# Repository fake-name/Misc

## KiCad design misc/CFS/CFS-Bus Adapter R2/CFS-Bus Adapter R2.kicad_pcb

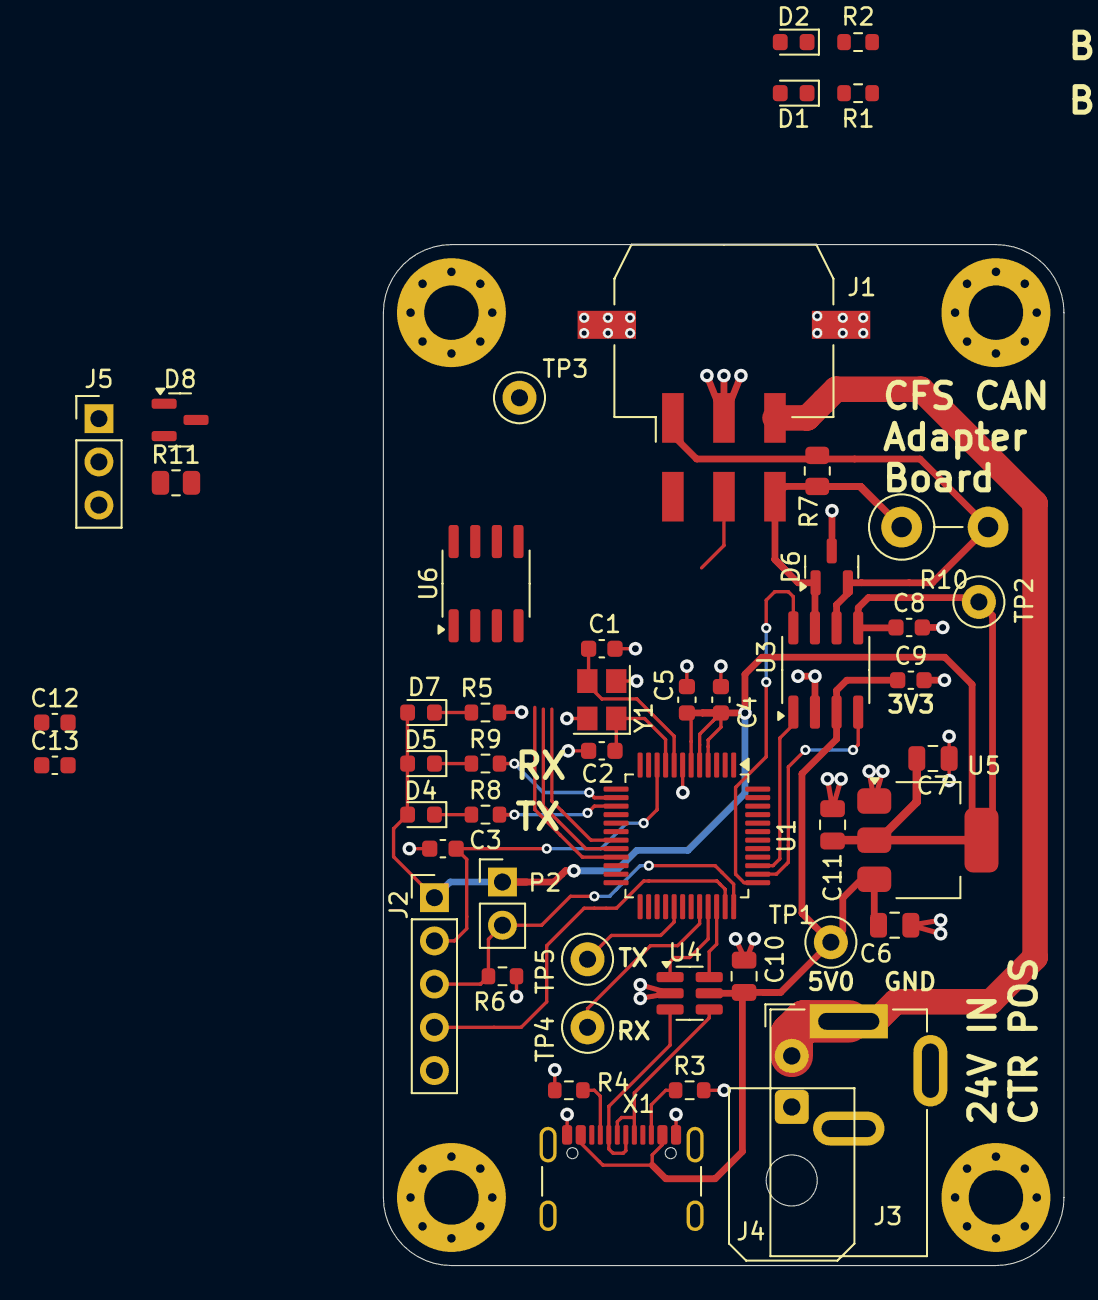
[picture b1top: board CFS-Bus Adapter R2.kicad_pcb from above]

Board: 2 copper layers, 40.0 x 60.0 mm, 53 parts (0 on the bottom side), 36 nets.

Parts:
C1, C2: 6p2_0603_C0G_5%_50V_-40C..125C_Chip-Capacitor; C_0603_1608Metric
C3, C4, C5: 100n; C_0603_1608Metric
C6, C7, C10, C11: 10u_0805_X7R_10%_10V_-40C..125C_Chip-Capacitor; C_0805_2012Metric
C8, C9, C12, C13: 100n_0603_X7R_10%_50V_-40C..125C_Chip-Capacitor; C_0603_1608Metric
D1, D2, D4, D5, D7: LED; LED_0603_1608Metric
D6, D8: NUP2105L; SOT-23
H1, H2, H3, H4: MountingHole; MountingHole_3.2mm_M3_Pad_Via
J1: Conn_02x03_Top_Bottom; Molex_Micro-Fit_3.0_43045-0610_2x03-1MP_P3.00mm_Horizontal
J2: Conn_01x05; PinHeader_1x05_P2.54mm_Vertical
J3: Barrel_Jack_Switch_MountingPin; BarrelJack_GCT_DCJ200-10-A_Horizontal
J4: Conn_01x02; Molex_Micro-Fit_3.0_43045-0200_2x01_P3.00mm_Horizontal
J5: Conn_01x03; PinHeader_1x03_P2.54mm_Vertical
P2: CONN_01X02; PinHeader_1x02_P2.54mm_Vertical
R1, R2: 5k1; R_0603_1608Metric
R3, R4: 5k1_0603_100mW_1%_E24_Chip-Resistor; R_0603_1608Metric
R5, R8, R9: 1k_0603_100mW_1%_E24_Chip-Resistor; R_0603_1608Metric
R6: 10k_0603_100mW_1%_E24_Chip-Resistor; R_0603_1608Metric
R7, R11: 120R_0805_125mW_1%_E24_Chip-Resistor; R_0805_2012Metric
R10: 120R_0805_125mW_1%_E24_Chip-Resistor; R_Axial_DIN0411_L9.9mm_D3.6mm_P5.08mm_Vertical
TP1, TP2, TP3: TP2.0mm; TestPoint_Loop_D1.80mm_Drill1.0mm_Beaded
TP4, TP5: TP1.0mm; TestPoint_Loop_D1.80mm_Drill1.0mm_Beaded
U1: STM32G0B1CBT; LQFP-48_7x7mm_P0.5mm
U3, U6: TJA1051T3; SOIC-8_3.9x4.9mm_P1.27mm
U4: IP4234CZ6; SC-74-6_1.55x2.9mm_P0.95mm
U5: AMS1117-3.3; SOT-223-3_TabPin2
X1: 629722000214_pasteInHole; USB_C_Receptacle_GCT_USB4105-xx-A_16P_TopMnt_Horizontal
Y1: 830108313809; Crystal_SMD_3225-4Pin_3.2x2.5mm

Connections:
+3V3: C4.1, C5.1, C7.1, C8.1, C11.1, C12.1, D4.2 (A), D5.2 (A), D7.2 (A), J2.1, P2.1, TP2.1, U1.4 (VBAT), U1.5 (VREF+), U1.6 (VDD/VDDA), U3.5 (VIO), U5.2 (VO), U6.5 (VIO)
+5V: C6.1, C9.1, C10.1, C13.1, D1.2 (A), D2.2 (A), TP1.1, U3.3 (VCC), U4.5 (VP), U5.3 (VI), U6.3 (VCC), X1.A4 (VBUS), X1.A9 (VBUS), X1.B4 (VBUS), X1.B9 (VBUS)
+24V: J1.3, J3.1, J4.2
/MCU/CAN1_RX: U1.38 (PD0), U3.4 (RXD)
/MCU/CAN1_S: U1.37 (PA15), U3.8 (S)
/MCU/CAN1_TX: U1.39 (PD1), U3.1 (TXD)
/MCU/CAN2_RX: U1.19 (PB0), U6.4 (RXD)
/MCU/CAN2_S: U1.21 (PB2), U6.8 (S)
/MCU/CAN2_TX: U1.20 (PB1), U6.1 (TXD)
/MCU/LED_RX: R9.2, U1.14 (PA3)
/MCU/LED_TX: R8.2, U1.15 (PA4)
/MCU/NRST: C3.1, J2.2, U1.10 (PF2/NRST)
/MCU/RX: TP4.1, U1.32 (PA10)
/MCU/SWCLK: J2.3, P2.2, R6.1, U1.36 (PA14/BOOT0)
/MCU/SWDIO: J2.4, U1.35 (PA13)
/MCU/TX: TP5.1, U1.29 (PA9)
/MCU/USB_{N}: U1.33 (PA11[PA9]), U4.1
/MCU/USB_{P}: U1.34 (PA12[PA10]), U4.6
/RS485-A: D6.1 (K), J1.6, R7.1, R10.1, U3.7 (CANH)
/RS485-B: D6.2 (K), J1.1, R7.2, R10.2, U3.6 (CANL)
/USB_N: U4.3, X1.A7 (DN1), X1.B7 (DN2)
/USB_P: U4.4, X1.A6 (DP1), X1.B6 (DP2)
GND: C1.1, C2.1, C3.2, C4.2, C5.2, C6.2, C7.2, C8.2, C9.2, C10.2, C11.2, C12.2, C13.2, D6.3 (A), D8.3 (A), J1.2, J1.MP, J2.5, J3.2, J3.3, J4.1, J5.2, R3.2, R4.2, R5.2, R6.2, TP3.1, U1.7 (VSS/VSSA), U3.2 (GND), U4.2 (VN), U5.1 (GND), U6.2 (GND), X1.A1 (GND), X1.B1 (GND), Y1.2 (GND), Y1.4 (GND)
unnamed: D1.1 (K), R1.1
unnamed: D2.1 (K), R2.1
unnamed: D4.1 (K), R8.1
unnamed: D5.1 (K), R9.1
unnamed: D7.1 (K), R5.1
unnamed: J1.4, R2.2
unnamed: J1.5, R1.2
unnamed: D8.1 (K), J5.1, R11.2, U6.6 (CANL)
unnamed: D8.2 (K), J5.3, R11.1, U6.7 (CANH)
unnamed: C1.2, U1.8 (PF0/OSC_IN), Y1.3 (C_{2})
unnamed: C2.2, U1.9 (PF1/OSC_OUT), Y1.1 (C_{1})
unnamed: R4.1, X1.A5 (CC1)
unnamed: R3.1, X1.B5 (CC2)

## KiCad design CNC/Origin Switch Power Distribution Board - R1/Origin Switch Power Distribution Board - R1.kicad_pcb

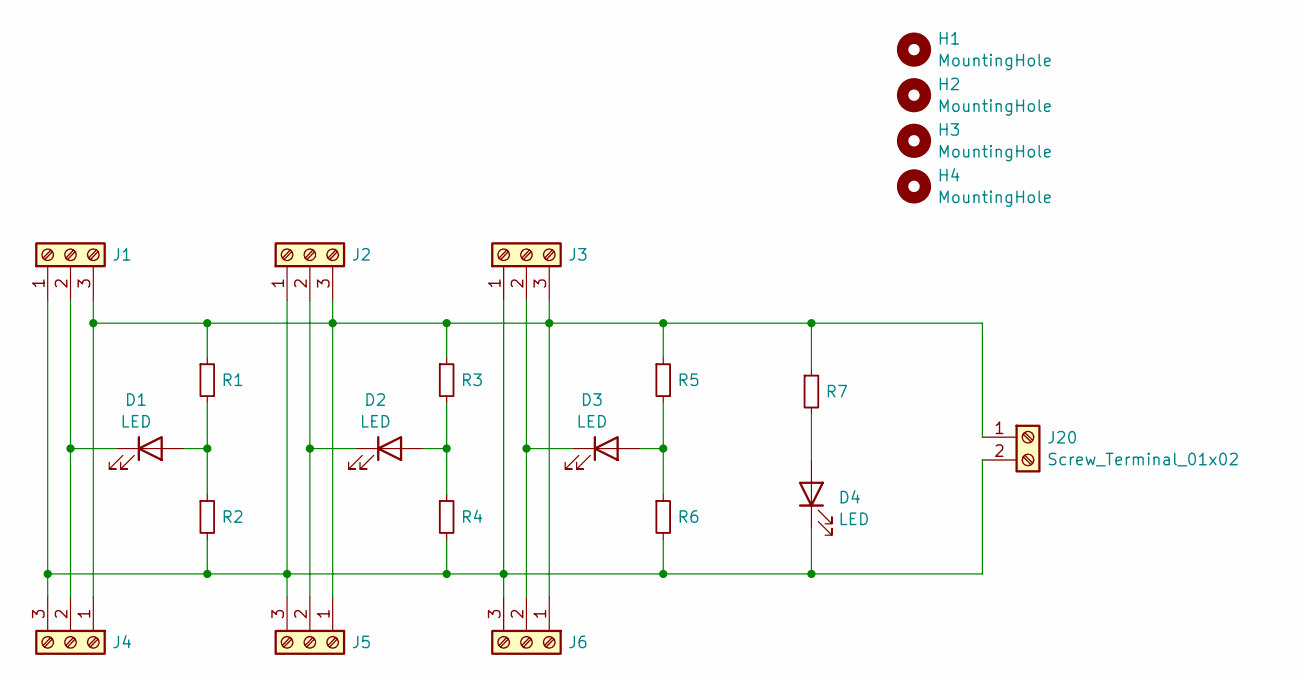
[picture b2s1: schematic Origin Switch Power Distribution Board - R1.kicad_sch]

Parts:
D1, D2, D3, D4: LED; LED_D5.0mm
H1, H2, H3, H4: MountingHole; MountingHole_3.2mm_M3_Pad_Via
J1, J2, J3, J4, J5, J6: Screw_Terminal_01x03; TerminalBlock_Phoenix_MKDS-1,5-3-5.08_1x03_P5.08mm_Horizont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
J20: Screw_Terminal_01x02; TerminalBlock_Phoenix_MKDS-1,5-2-5.08_1x02_P5.08mm_Horizont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
R1, R2, R3, R4, R5, R6, R7: R_Small; R_Axial_DIN0204_L3.6mm_D1.6mm_P7.62mm_Horizontal

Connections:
unnamed: D1.2 (A), R1.2, R2.1
unnamed: D1.1 (K), J1.2, J4.2
unnamed: D2.2 (A), R3.2, R4.1
unnamed: D2.1 (K), J2.2, J5.2
unnamed: D3.2 (A), R5.2, R6.1
unnamed: D3.1 (K), J3.2, J6.2
unnamed: D4.2 (A), R7.2
unnamed: D4.1 (K), J1.1, J2.1, J3.1, J4.3, J5.3, J6.3, J20.2, R2.2, R4.2, R6.2
unnamed: J1.3, J2.3, J3.3, J4.1, J5.1, J6.1, J20.1, R1.1, R3.1, R5.1, R7.1

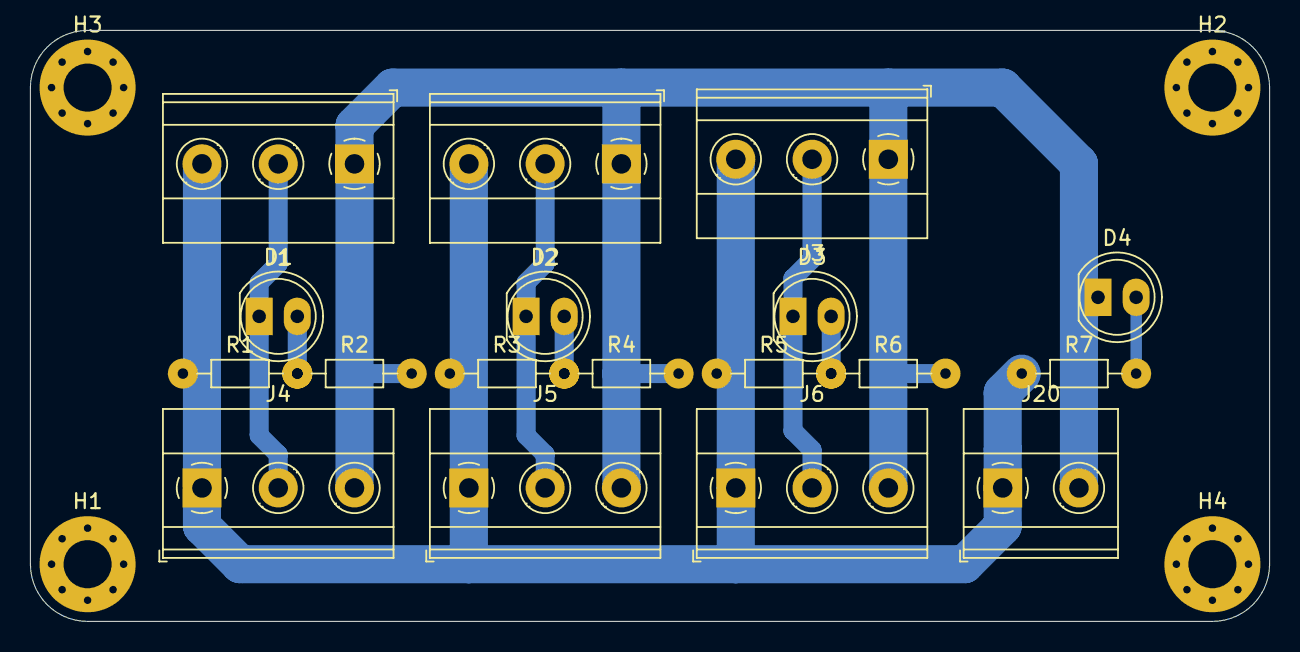
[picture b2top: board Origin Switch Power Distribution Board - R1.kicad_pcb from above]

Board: 2 copper layers, 82.5 x 39.4 mm, 22 parts (0 on the bottom side), 9 nets.

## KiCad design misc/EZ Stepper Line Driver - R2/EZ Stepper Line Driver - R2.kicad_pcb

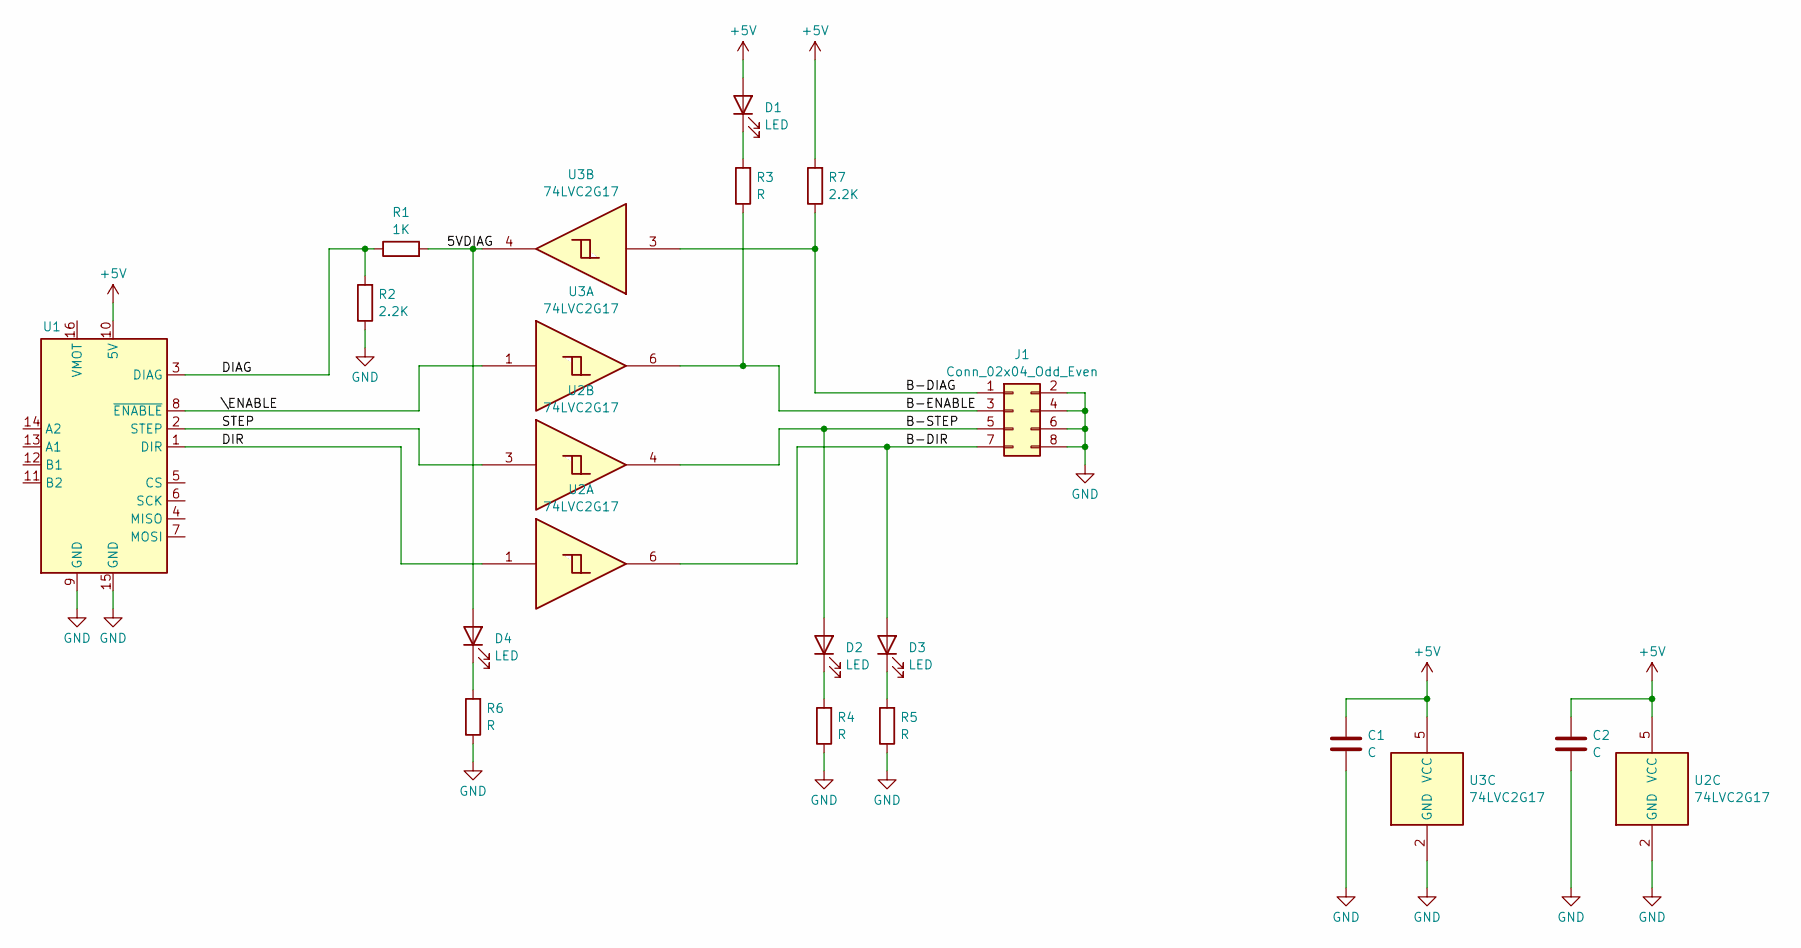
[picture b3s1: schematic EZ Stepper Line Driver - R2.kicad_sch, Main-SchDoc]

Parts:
C1, C2: C; C_0603_1608Metric; LCSC C15849
D1, D2, D3, D4: LED; LED_0603_1608Metric; LCSC C2286
J1: Conn_02x04_Odd_Even; Molex_PicoBlade_53261-0871_1x08-1MP_P1.25mm_Horizontal; LCSC C293349
R1: 1K; R_0603_1608Metric; LCSC C21190
R2, R7: 2.2K; R_0603_1608Metric; LCSC C4190
R3, R4, R5, R6: R; R_0603_1608Metric; LCSC C4190
U1: EZ Driver Interface; EZ_Stepper_Edge_Connector
U2, U3: 74LVC2G17; SOT-363_SC-70-6; LCSC C10429

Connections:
+5V: C1.1, C2.1, D1.2 (A), R7.2, U1.10 (5V), U2.5 (VCC), U3.5 (VCC)
/5VDIAG: D4.2 (A), R1.2, U3.4
/B-DIAG: J1.1, R7.1, U3.3
/B-DIR: D3.2 (A), J1.7, U2.6
/B-ENABLE: J1.3, R3.1, U3.6
/B-STEP: D2.2 (A), J1.5, U2.4
/DIAG: R1.1, R2.2, U1.3 (DIAG)
/DIR: U1.1 (DIR), U2.1
/STEP: U1.2 (STEP), U2.3
/\ENABLE: U1.8 (~ENABLE), U3.1
GND: C1.2, C2.2, J1.2, J1.4, J1.6, J1.8, J1.MP, R2.1, R4.1, R5.1, R6.1, U1.9 (GND), U1.15 (GND), U2.2 (GND), U3.2 (GND)
unnamed: D1.1 (K), R3.2
unnamed: D2.1 (K), R4.2
unnamed: D3.1 (K), R5.2
unnamed: D4.1 (K), R6.2

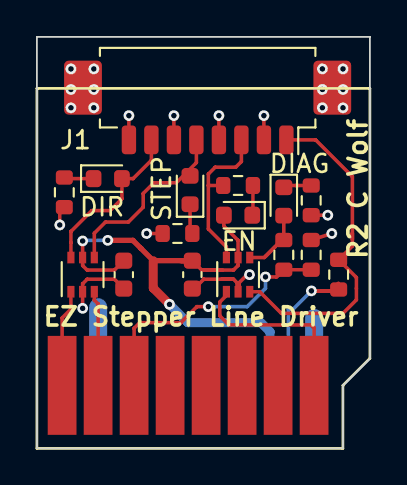
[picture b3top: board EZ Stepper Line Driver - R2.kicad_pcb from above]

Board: 2 copper layers, 18.5 x 22.9 mm, 17 parts (0 on the bottom side), 15 nets.

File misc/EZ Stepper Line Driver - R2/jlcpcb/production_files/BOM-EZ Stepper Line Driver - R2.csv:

Comment,Designator,Footprint,LCSC,Quantity
C,"C1,C2",C_0603_1608Metric,C15849,2
1K,R1,R_0603_1608Metric,C21190,1
LED,"D1,D2,D3,D4",LED_0603_1608Metric,C2286,4
Conn_02x04_Odd_Even,J1,Molex_PicoBlade_53261-0871_1x08-1MP_P1.25mm_Horizontal,C293349,1
2.2K,"R2,R3,R4,R5,R6,R7",R_0603_1608Metric,C4190,6
74LVC2G17,"U2,U3",SOT-363_SC-70-6,C50714,2

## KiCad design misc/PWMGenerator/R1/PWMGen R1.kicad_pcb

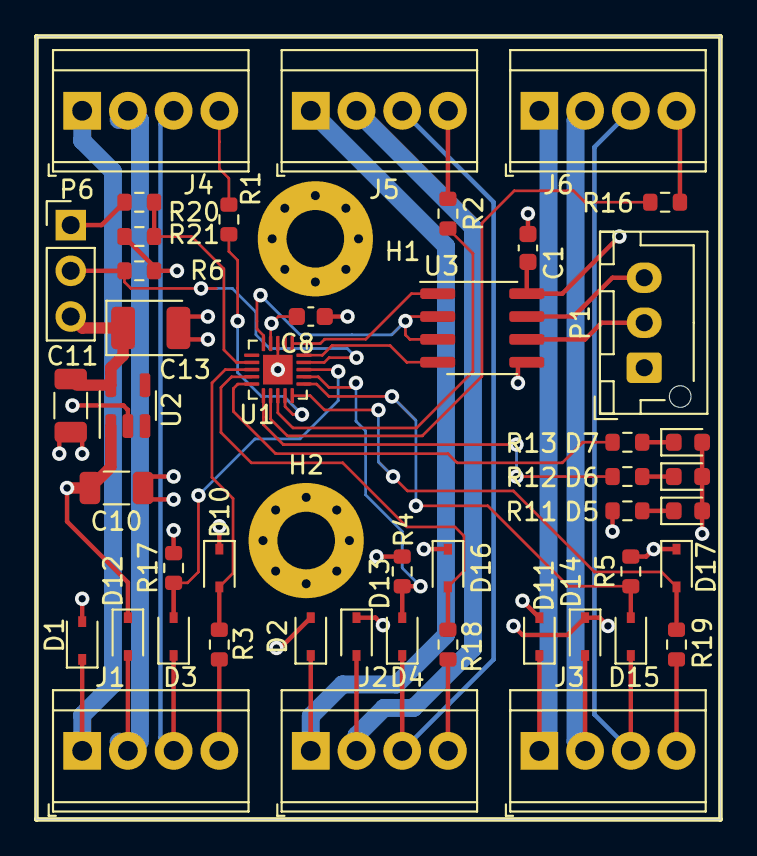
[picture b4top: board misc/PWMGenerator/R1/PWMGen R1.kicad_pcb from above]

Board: 4 copper layers, 38.0 x 43.5 mm, 48 parts (0 on the bottom side), 39 nets.

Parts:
C1, C8: Cap; C_0603_1608Metric
C10, C11: Cap; C_1206_3216Metric
C13: 100 uF; CP_EIA-3528-21_Kemet-B
D1, D2, D3, D4, D10, D11, D12, D13, D14, D15, D16, D17: Schottky Diode; D_SOD-323
D5, D6, D7: LED0; D_0603_1608Metric
H1, H2: MountingHole; MountingHole_3.2mm_M3_Pad_Via
J1, J2, J3, J4, J5, J6: Conn_01x04; TerminalBlock_TE_282834-4_1x04_P2.54mm_Horizontal
P1: Header 3; JST_XH_B3B-XH-AM_1x03_P2.50mm_Vertical
P6: Header 3; PinHeader_1x03_P2.54mm_Vertical
R1, R2, R3, R4, R5, R6, R16, R17, R18, R19, R20, R21: Res Semi Small; R_0603_1608Metric
R11, R12, R13: Res Semi; R_0603_1608Metric
U1: ATTiny1616-MFR; QFN-20-1EP_3x3mm_P0.4mm_EP1.65x1.65mm
U2: TPS70950; SOT-23-5
U3: THVD1400D; SOIC-8_3.9x4.9mm_P1.27mm

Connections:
5V: C1.2, C8.2, C11.2, C13.1, D10.1, D16.1, D17.1, P6.3, R4.2, R5.2, R6.2, R11.2, R17.2, R21.2, U1.4 (VDD), U2.5 (Out), U3.8 (VCC)
12V: C10.2, D12.1, D13.1, D14.1, U2.1 (In)
/F12V1: D12.2, J1.2, J4.2
/F12V2: D13.2, J2.2, J5.2
/F12V3: D14.2, J3.2, J6.2
/FGND1: D1.1, J1.1, J4.1
/FGND2: D2.1, J2.1, J5.1
/FGND3: D11.1, J3.1, J6.1
/PWM_IN_1: J1.4, R3.1
/PWM_IN_2: J2.4, R18.1
/PWM_IN_3: J3.4, R19.1
/PWM_OUT1: J4.4, R1.1
/PWM_OUT2: J5.4, R2.1
/PWM_OUT3: J6.4, R16.1
/RXD: U1.1 (PA2/SCL), U3.1 (RO)
/TXD: U1.20 (PA1/SDA), U3.4 (DI)
/Tach1: D3.1, J1.3, J4.3
/Tach2: D4.1, J2.3, J5.3
/Tach3: D15.1, J3.3, J6.3
/UPDI/~RESET: P6.2, R6.1, U1.19 (PA0/~RESET/UPDI)
/XDIR: U1.5 (PA4), U3.2 (~RE), U3.3 (DE)
GND: C1.1, C8.1, C10.1, C11.1, C13.2, D1.2, D2.2, D5.2, D6.2, D7.2, D11.2, P1.1, P6.1, R20.1, U1.3 (GND), U1.21 (PAD), U2.2 (Gnd), U3.5 (GND)
unnamed: D5.1, R11.1
unnamed: D6.1, R12.1
unnamed: D7.1, R13.1
unnamed: R20.2, R21.1, U1.7 (PA6)
unnamed: D10.2, R3.2, U1.8 (PA7)
unnamed: R1.2, U1.14 (PB0)
unnamed: R2.2, U1.13 (PB1)
unnamed: R16.2, U1.12 (PB2/TOSC2)
unnamed: R12.2, U1.11 (PB3/TOSC1)
unnamed: R13.2, U1.10 (PB4)
unnamed: D16.2, R18.2, U1.9 (PB5)
unnamed: D17.2, R19.2, U1.15 (PC0)
unnamed: D15.2, R5.1, U1.16 (PC1)
unnamed: D4.2, R4.1, U1.17 (PC2)
unnamed: D3.2, R17.1, U1.18 (PC3)
unnamed: P1.2, U3.6 (A)
unnamed: P1.3, U3.7 (B)

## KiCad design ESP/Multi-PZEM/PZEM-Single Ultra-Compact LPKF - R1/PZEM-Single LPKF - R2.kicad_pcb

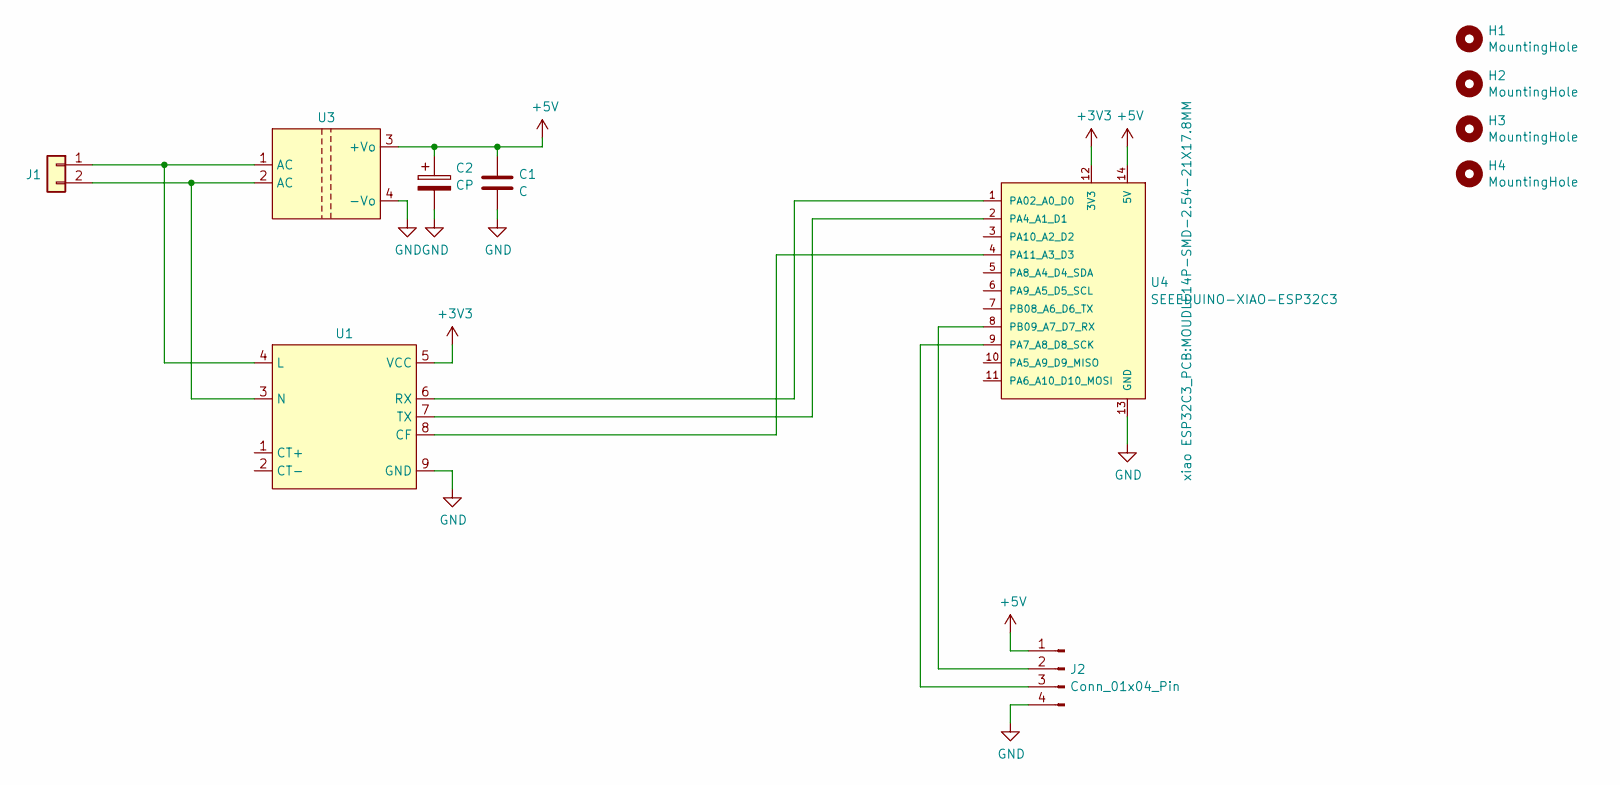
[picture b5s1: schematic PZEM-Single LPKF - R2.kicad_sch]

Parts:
C1: C; C_1206_3216Metric
C2: CP; CP_EIA-7360-38_Kemet-E_Pad2.25x4.25mm_HandSolder
H1, H2, H3, H4: MountingHole; MountingHole_3.2mm_M3_Pad
J1: Conn_01x02; PhoenixContact_MCV_1,5_2-G-5.08_1x02_P5.08mm_Vertical
J2: Conn_01x04_Pin; JST_XH_B4B-XH-A_1x04_P2.50mm_Vertical
U1: PZEM-004T-100A-D-P
U3: HLK-PM01
U4: SEEEDUINO-XIAO-ESP32C3; MOUDLE14P-SMD-2.54-21X17.8MM

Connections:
+3V3: U1.5 (VCC), U4.12 (3V3)
+5V: C1.1, C2.1, J2.1, U3.3 (+Vo), U4.14 (5V)
GND: C1.2, C2.2, J2.4, U1.9 (GND), U3.4 (-Vo), U4.13 (GND)
unnamed: J1.1, U1.4 (L), U3.1 (AC)
unnamed: J1.2, U1.3 (N), U3.2 (AC)
unnamed: J2.2, U4.8 (PB09_A7_D7_RX)
unnamed: J2.3, U4.9 (PA7_A8_D8_SCK)
unnamed: U1.8 (CF), U4.4 (PA11_A3_D3)
unnamed: U1.6 (RX), U4.1 (PA02_A0_D0)
unnamed: U1.7 (TX), U4.2 (PA4_A1_D1)

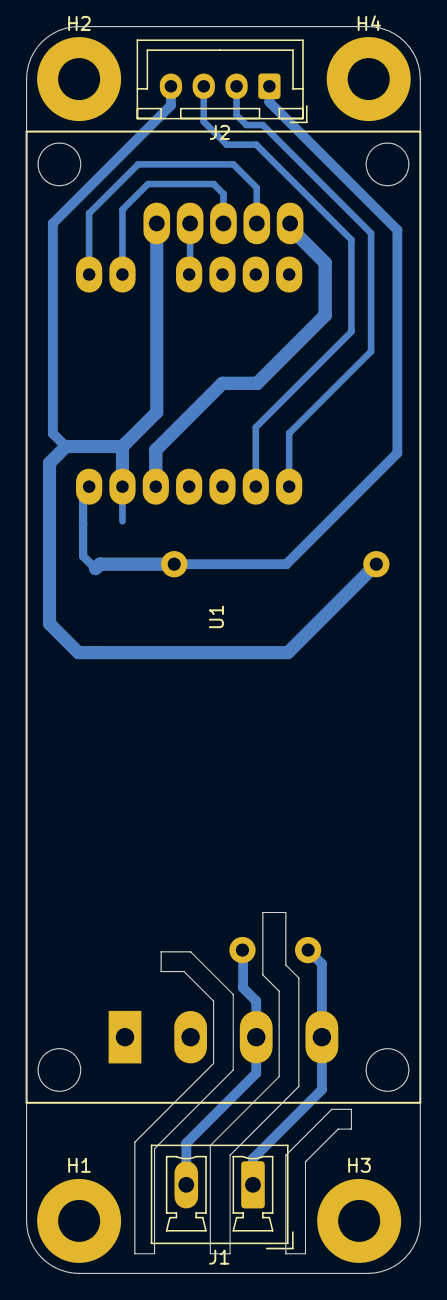
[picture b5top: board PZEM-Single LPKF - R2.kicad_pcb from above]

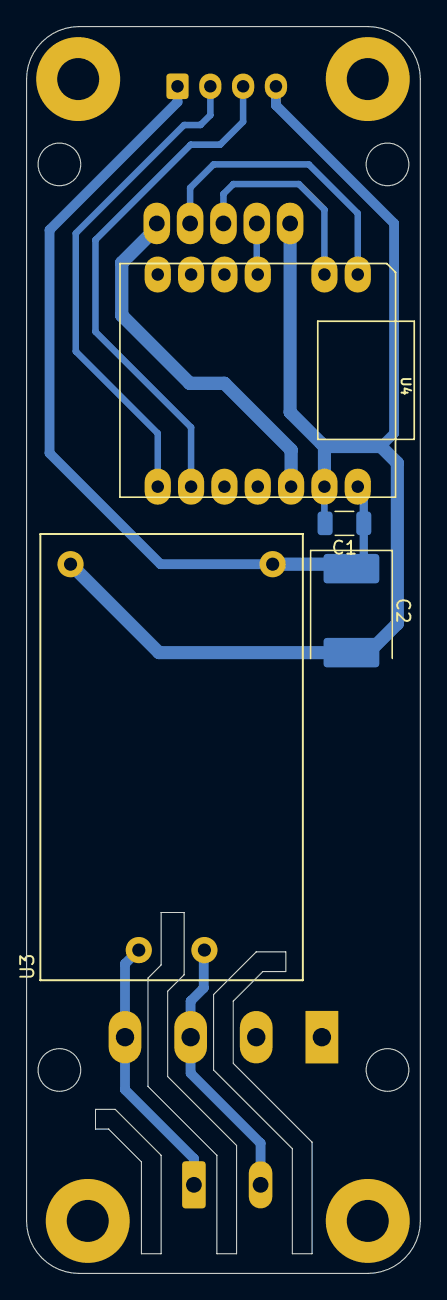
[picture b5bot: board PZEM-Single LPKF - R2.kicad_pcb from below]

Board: 2 copper layers, 30.0 x 95.0 mm, 11 parts (4 on the bottom side), 10 nets.

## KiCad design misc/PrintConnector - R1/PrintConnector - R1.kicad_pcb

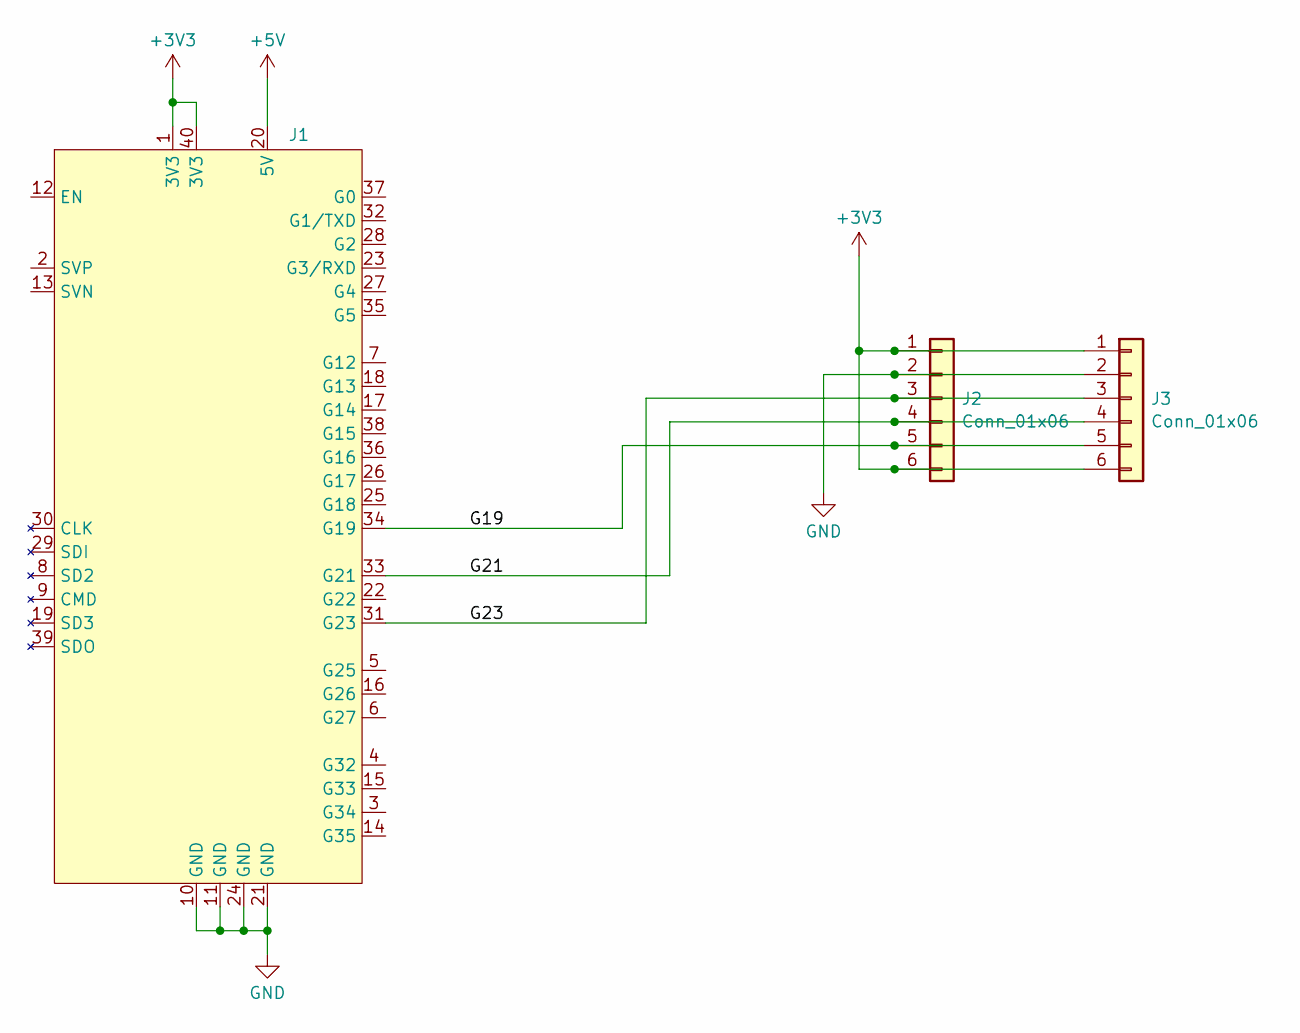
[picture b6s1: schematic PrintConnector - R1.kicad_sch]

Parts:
J1: ESP32_Relay_X2
J2: Conn_01x06; JST_XH_B6B-XH-A_1x06_P2.50mm_Vertical
J3: Conn_01x06; Molex_PicoBlade_53261-0671_1x06-1MP_P1.25mm_Horizontal

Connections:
+3V3: J1.1 (3V3), J1.40 (3V3), J2.1, J2.6, J3.1, J3.6
+5V: J1.20 (5V)
/G19: J1.34 (G19), J2.5, J3.5
/G21: J1.33 (G21), J2.4, J3.4
/G23: J1.31 (G23), J2.3, J3.3
GND: J1.10 (GND), J1.11 (GND), J1.21 (GND), J1.24 (GND), J2.2, J3.2

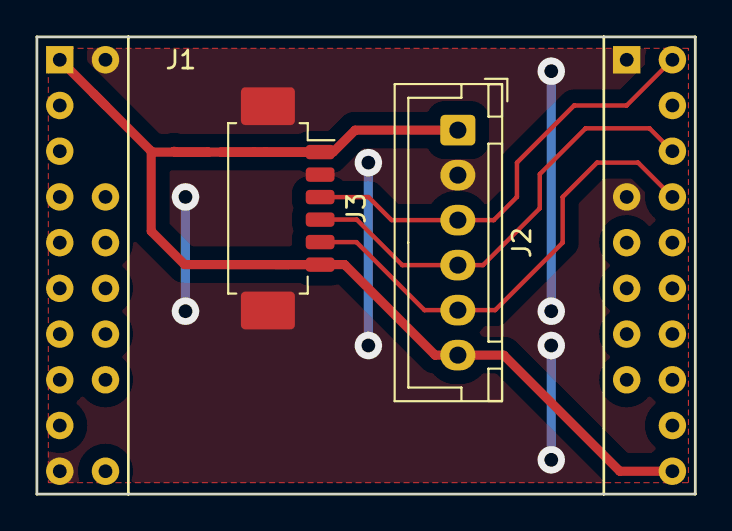
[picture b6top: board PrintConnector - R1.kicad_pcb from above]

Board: 2 copper layers, 36.6 x 25.4 mm, 3 parts (0 on the bottom side), 5 nets.

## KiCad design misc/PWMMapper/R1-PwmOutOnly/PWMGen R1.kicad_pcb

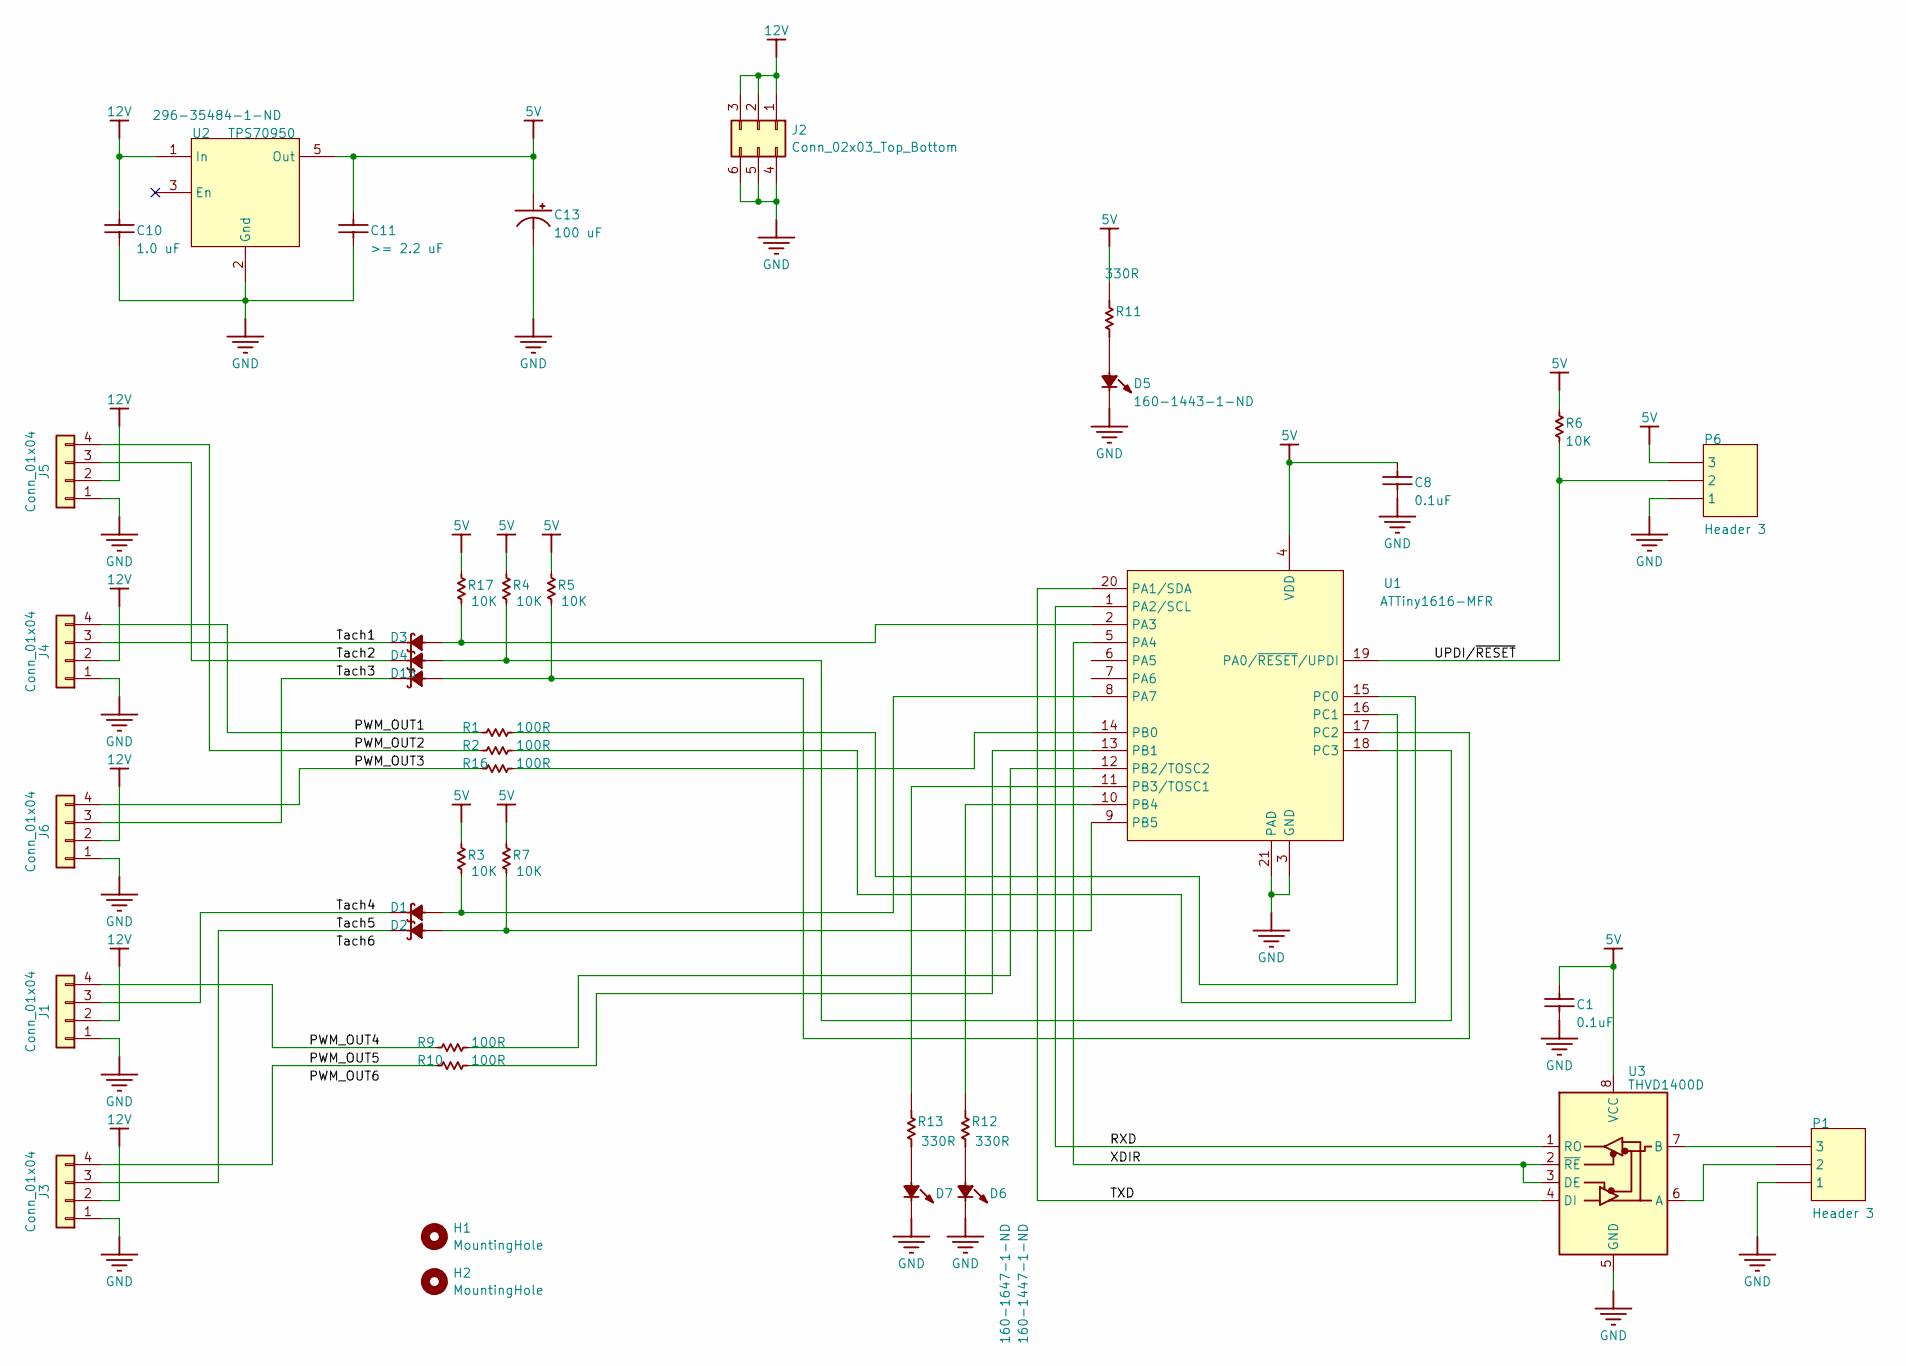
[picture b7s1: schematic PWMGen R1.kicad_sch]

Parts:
C1, C8: 0.1uF; C_0603_1608Metric; LCSC C1623
C10: 1.0 uF; C_1206_3216Metric; LCSC C50254
C11: >= 2.2 uF; C_1206_3216Metric; LCSC C50254
C13: 100 uF; CP_EIA-3528-21_Kemet-B; LCSC C2798043
D1, D2, D3, D4, D15: Schottky Diode; D_SOD-323; LCSC C191023
D5, D6, D7: LED0; D_0603_1608Metric; LCSC C2286
H1, H2: MountingHole; MountingHole_3.2mm_M3_Pad_Via
J1, J3, J4, J5, J6: Conn_01x04; TerminalBlock_TE_282834-4_1x04_P2.54mm_Horizontal
J2: Conn_02x03_Top_Bottom; Molex_Mini-Fit_Jr_5566-06A_2x03_P4.20mm_Vertical
P1: Header 3; JST_XH_B3B-XH-AM_1x03_P2.50mm_Vertical
P6: Header 3; PinHeader_1x03_P2.54mm_Vertical
R1, R2, R9, R10, R16: 100R; R_0603_1608Metric; LCSC C22775
R3, R4, R5, R6, R7, R17: 10K; R_0603_1608Metric; LCSC C25804
R11, R12, R13: 330R; R_0603_1608Metric; LCSC C23138
U1: ATTiny1616-MFR; QFN-20-1EP_3x3mm_P0.4mm_EP1.65x1.65mm; LCSC C152217
U2: TPS70950; SOT-23-5
U3: THVD1400D; SOIC-8_3.9x4.9mm_P1.27mm; LCSC C3235232

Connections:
5V: C1.2, C8.2, C11.2, C13.1, P6.3, R3.2, R4.2, R5.2, R6.2, R7.2, R11.2, R17.2, U1.4 (VDD), U2.5 (Out), U3.8 (VCC)
12V: C10.2, J1.2, J2.1, J2.2, J2.3, J3.2, J4.2, J5.2, J6.2, U2.1 (In)
/PWM_OUT1: J4.4, R1.1
/PWM_OUT2: J5.4, R2.1
/PWM_OUT3: J6.4, R16.1
/PWM_OUT4: J1.4, R9.1
/PWM_OUT5: J3.4, R10.1
/RXD: U1.1 (PA2/SCL), U3.1 (RO)
/TXD: U1.20 (PA1/SDA), U3.4 (DI)
/Tach1: D3.1, J4.3
/Tach2: D4.1, J5.3
/Tach3: D15.1, J6.3
/Tach4: D1.1, J1.3
/Tach5: D2.1, J3.3
/UPDI/~RESET: P6.2, R6.1, U1.19 (PA0/~RESET/UPDI)
/XDIR: U1.5 (PA4), U3.2 (~RE), U3.3 (DE)
GND: C1.1, C8.1, C10.1, C11.1, C13.2, D5.2, D6.2, D7.2, J1.1, J2.4, J2.5, J2.6, J3.1, J4.1, J5.1, J6.1, P1.1, P6.1, U1.3 (GND), U1.21 (PAD), U2.2 (Gnd), U3.5 (GND)
unnamed: D5.1, R11.1
unnamed: D6.1, R12.1
unnamed: D7.1, R13.1
unnamed: D3.2, R17.1, U1.2 (PA3)
unnamed: D1.2, R3.1, U1.8 (PA7)
unnamed: R16.2, U1.14 (PB0)
unnamed: R10.2, U1.13 (PB1)
unnamed: R9.2, U1.12 (PB2/TOSC2)
unnamed: R13.2, U1.11 (PB3/TOSC1)
unnamed: R12.2, U1.10 (PB4)
unnamed: D2.2, R7.1, U1.9 (PB5)
unnamed: R2.2, U1.15 (PC0)
unnamed: R1.2, U1.16 (PC1)
unnamed: D15.2, R5.1, U1.17 (PC2)
unnamed: D4.2, R4.1, U1.18 (PC3)
unnamed: P1.2, U3.6 (A)
unnamed: P1.3, U3.7 (B)

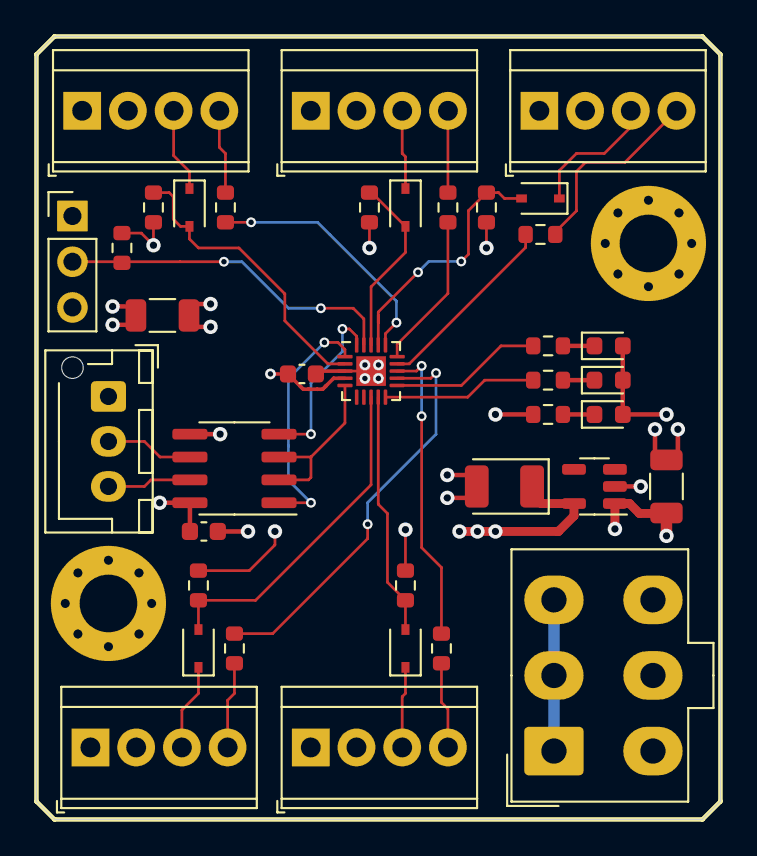
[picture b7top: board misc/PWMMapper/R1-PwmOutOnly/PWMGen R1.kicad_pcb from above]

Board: 4 copper layers, 38.0 x 43.5 mm, 40 parts (0 on the bottom side), 34 nets.

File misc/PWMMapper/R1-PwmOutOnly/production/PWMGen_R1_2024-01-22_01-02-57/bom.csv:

Designator,Footprint,Quantity,Value,LCSC Part #
"C1, C8",0603,2,0.1uF,
C10,1206,1,1.0 uF,
C11,1206,1,>= 2.2 uF,
C13,CP_EIA-3528-21_Kemet-B,1,100 uF,
"D1, D15, D2, D3, D4",D_SOD-323,5,Schottky Diode,
"D5, D6, D7",0603,3,LED0,
"J1, J3, J4, J5, J6",TerminalBlock_TE_282834-4_1x04_P2.54mm_Horizontal,5,Conn_01x04,
J2,Molex_Mini-Fit_Jr_5566-06A_2x03_P4.20mm_Vertical,1,Conn_02x03_Top_Bottom,
P1,JST_XH_B3B-XH-AM_1x03_P2.50mm_Vertical,1,Header 3,
P6,PinHeader_1x03_P2.54mm_Vertical,1,Header 3,
"R1, R10, R16, R2, R9",0603,5,100R,
"R11, R12, R13",0603,3,330R,
"R17, R3, R4, R5, R6, R7",0603,6,10K,
U1,QFN-20-1EP_3x3mm_P0.4mm_EP1.65x1.65mm,1,ATTiny1616-MFR,
U2,SOT-23-5,1,TPS70950,
U3,SOIC-8_3.9x4.9mm_P1.27mm,1,THVD1400D,

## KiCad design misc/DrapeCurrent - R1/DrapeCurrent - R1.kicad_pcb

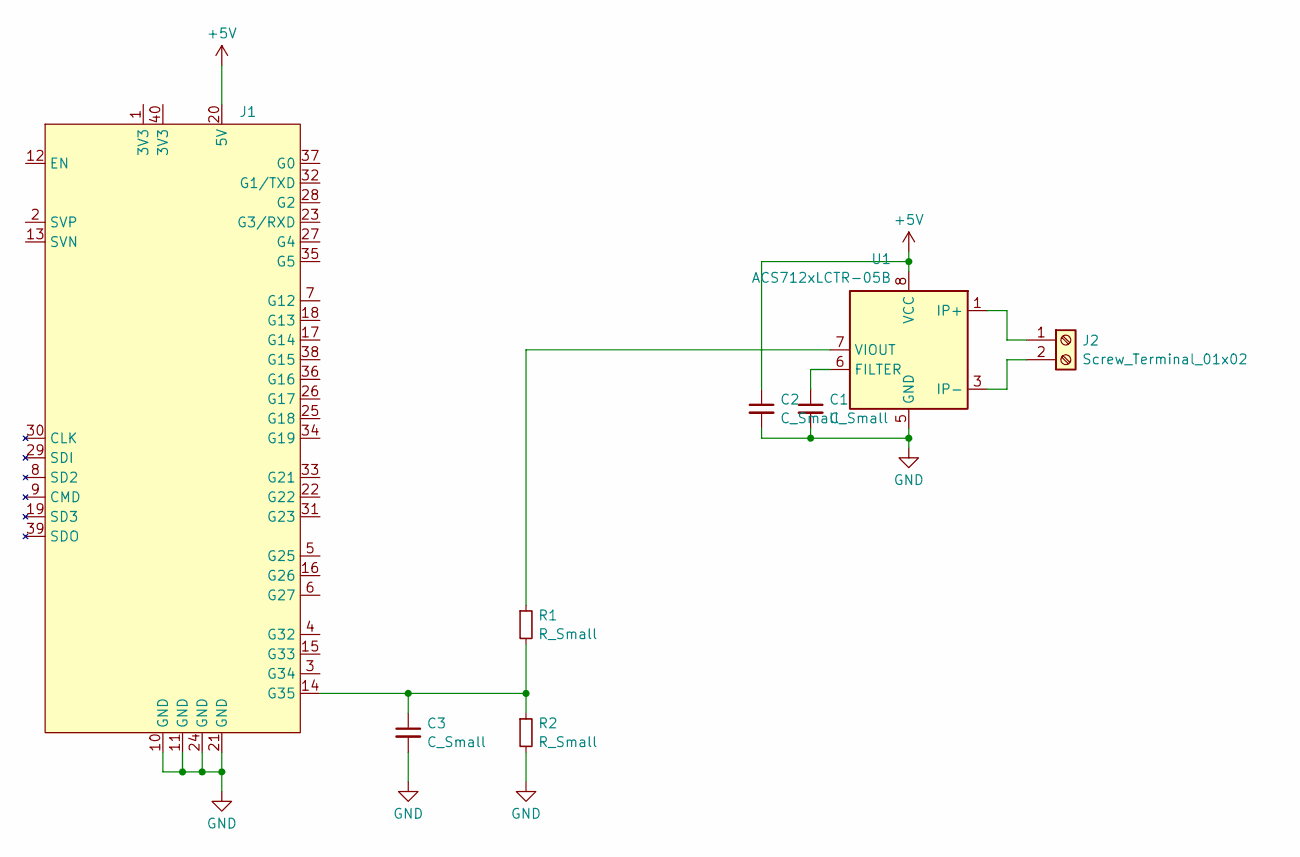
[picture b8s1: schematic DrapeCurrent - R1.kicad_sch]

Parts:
C1, C2, C3: C_Small; C_1206_3216Metric_Pad1.33x1.80mm_HandSolder
J1: ESP32_Relay_X2
J2: Screw_Terminal_01x02; TerminalBlock_Altech_AK300-2_P5.00mm
R1, R2: R_Small; R_Axial_DIN0207_L6.3mm_D2.5mm_P10.16mm_Horizontal
U1: ACS712xLCTR-05B; SOIC-8_3.9x4.9mm_P1.27mm

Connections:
+5V: C2.1, J1.20 (5V), U1.8 (VCC)
GND: C1.2, C2.2, C3.2, J1.10 (GND), J1.11 (GND), J1.21 (GND), J1.24 (GND), R2.2, U1.5 (GND)
unnamed: C3.1, J1.14 (G35), R1.2, R2.1
unnamed: J2.1, U1.1 (IP+), U1.2 (IP+)
unnamed: J2.2, U1.3 (IP-), U1.4 (IP-)
unnamed: C1.1, U1.6 (FILTER)
unnamed: R1.1, U1.7 (VIOUT)

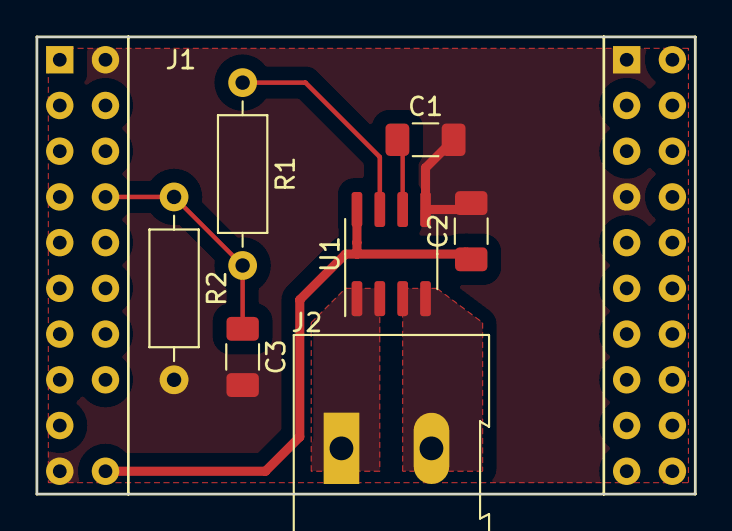
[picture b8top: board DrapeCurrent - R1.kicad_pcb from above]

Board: 2 copper layers, 36.6 x 25.4 mm, 8 parts (0 on the bottom side), 7 nets.
